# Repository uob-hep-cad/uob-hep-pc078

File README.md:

# uob-hep-pc078

XLZD OD preamplifier based on XENONnT design

Based on circuit in J. Wulf, Direct Dark Matter Search with XENON1T and Developments for Multi-Ton Liquid Xenon Detectors

[Circuit Schematic](./hardware/KiCAD/xlzd_xenonnt_amplifier_test/xlzd_xenonnt_amplifier_test_schematic_8jun26_01.pdf)

3D rendering of PCB:

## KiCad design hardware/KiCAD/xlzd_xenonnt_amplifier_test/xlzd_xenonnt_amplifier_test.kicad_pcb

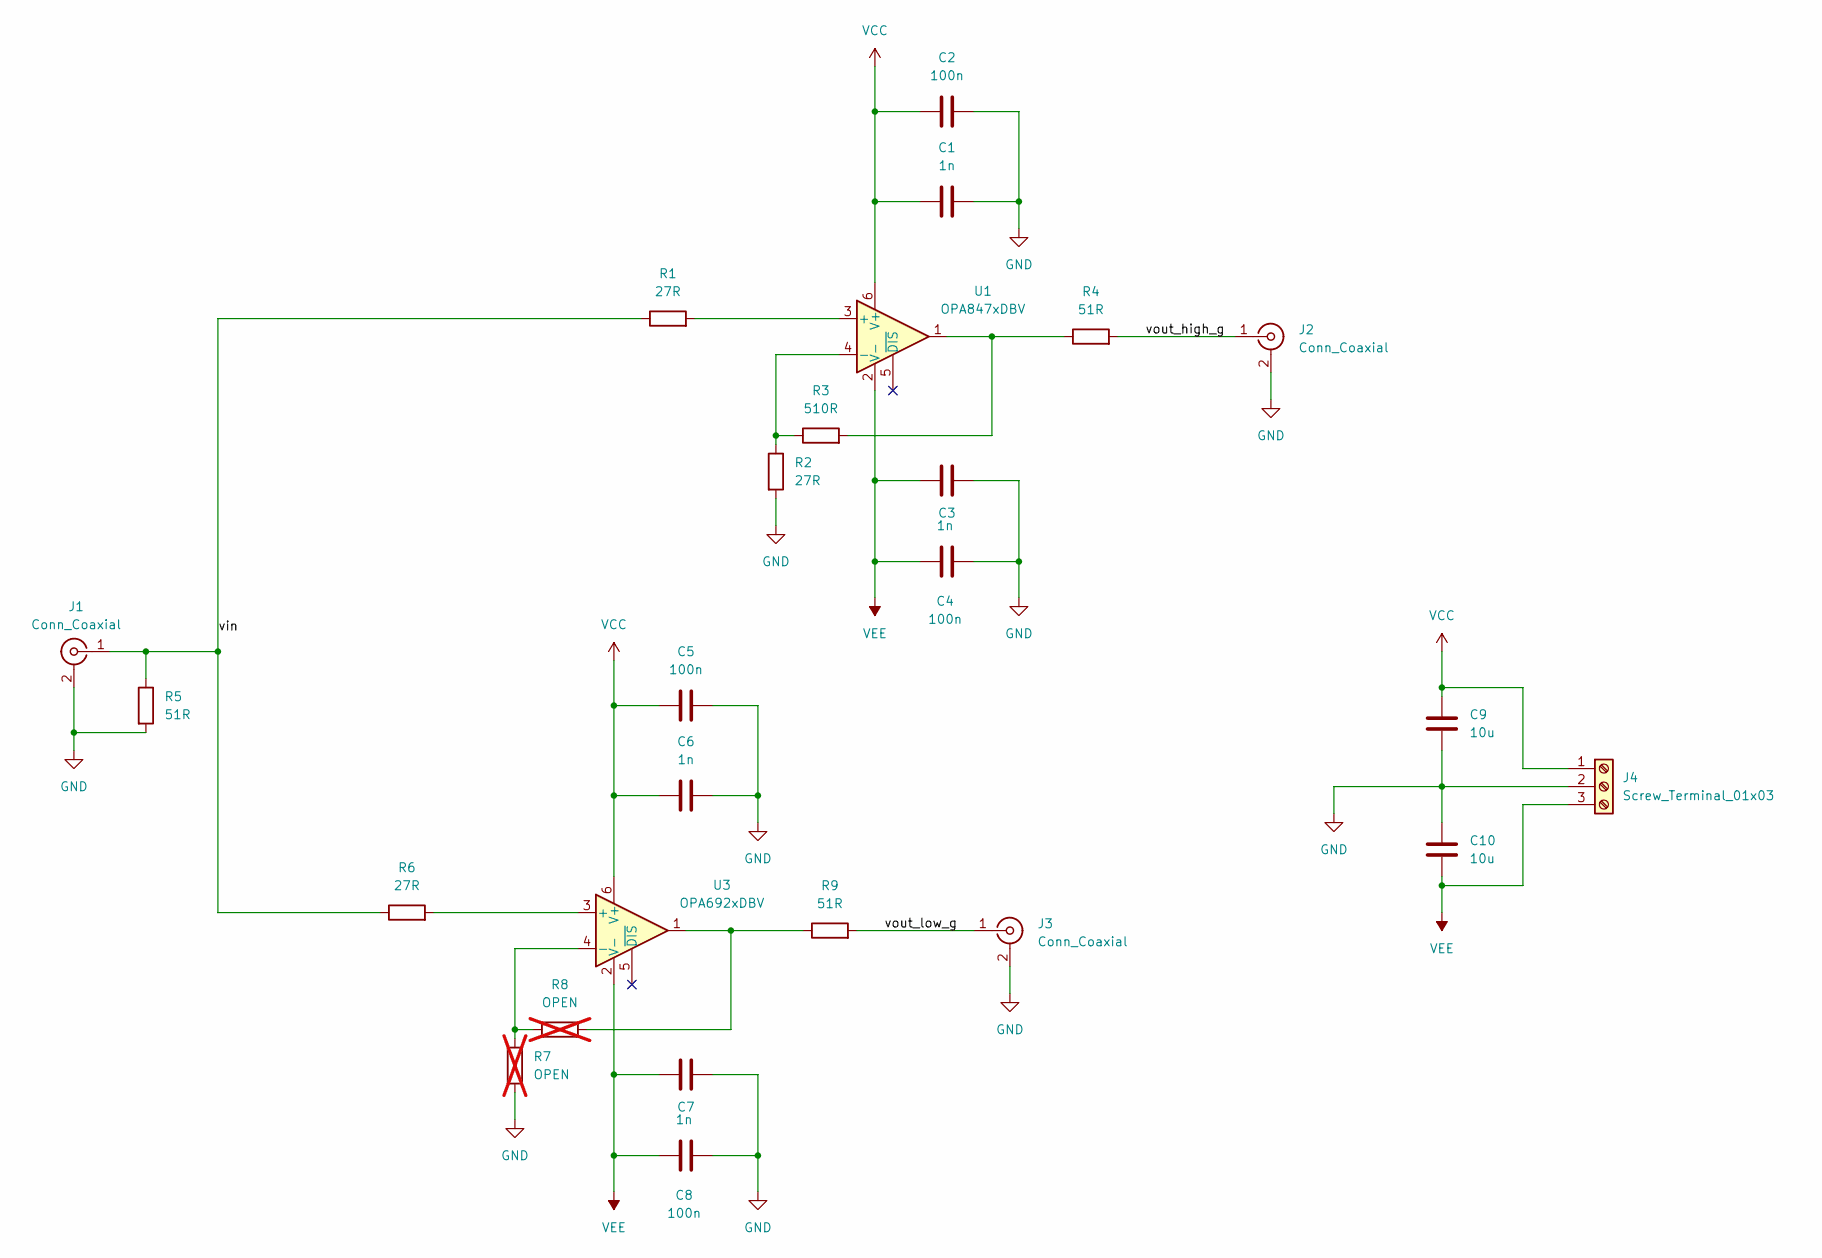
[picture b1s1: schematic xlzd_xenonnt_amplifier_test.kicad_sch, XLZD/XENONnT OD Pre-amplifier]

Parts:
C1, C3, C6, C7: 1n; C_0402_1005Metric_Pad0.74x0.62mm_HandSolder
C2, C4, C5, C8: 100n; C_0603_1608Metric_Pad1.08x0.95mm_HandSolder
C9, C10: 10u; C_1210_3225Metric_Pad1.33x2.70mm_HandSolder
J1, J2, J3: Conn_Coaxial; SMA_Amphenol_132289_EdgeMount
J4: Screw_Terminal_01x03; TerminalBlock_Phoenix_MPT-0,5-3-2.54_1x03_P2.54mm_Horizontal
R1, R2, R6: 27R; R_0603_1608Metric_Pad0.98x0.95mm_HandSolder
R3: 510R; R_0603_1608Metric_Pad0.98x0.95mm_HandSolder
R4, R5, R9: 51R; R_0603_1608Metric_Pad0.98x0.95mm_HandSolder
R7, R8: OPEN; R_0603_1608Metric_Pad0.98x0.95mm_HandSolder; not fitted
U1: OPA847xDBV; SOT-23-6
U3: OPA692xDBV; SOT-23-6

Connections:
/vin: J1.1 (In), R1.1, R5.1, R6.1
/vout_high_g: J2.1 (In), R4.2
/vout_low_g: J3.1 (In), R9.2
GND: C1.2, C2.2, C3.2, C4.2, C5.2, C6.2, C7.2, C8.2, C9.2, C10.1, J1.2 (Ext), J2.2 (Ext), J3.2 (Ext), J4.2, R2.2, R5.2, R7.2
unnamed: R3.2, R4.1, U1.1
unnamed: R8.2, R9.1, U3.1
unnamed: R1.2, U1.3 (+)
unnamed: R2.1, R3.1, U1.4 (-)
unnamed: R6.2, U3.3 (+)
unnamed: R7.1, R8.1, U3.4 (-)
VCC: C1.1, C2.1, C5.1, C6.1, C9.1, J4.1, U1.6 (V+), U3.6 (V+)
VEE: C3.1, C4.1, C7.1, C8.1, C10.2, J4.3, U1.2 (V-), U3.2 (V-)

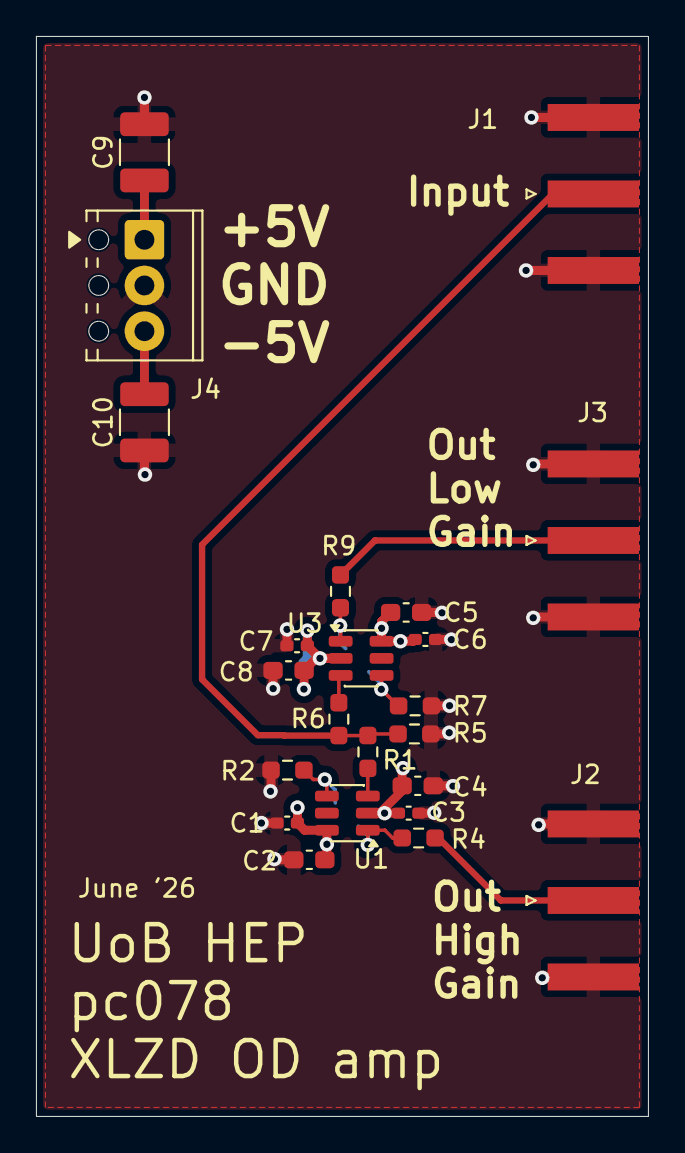
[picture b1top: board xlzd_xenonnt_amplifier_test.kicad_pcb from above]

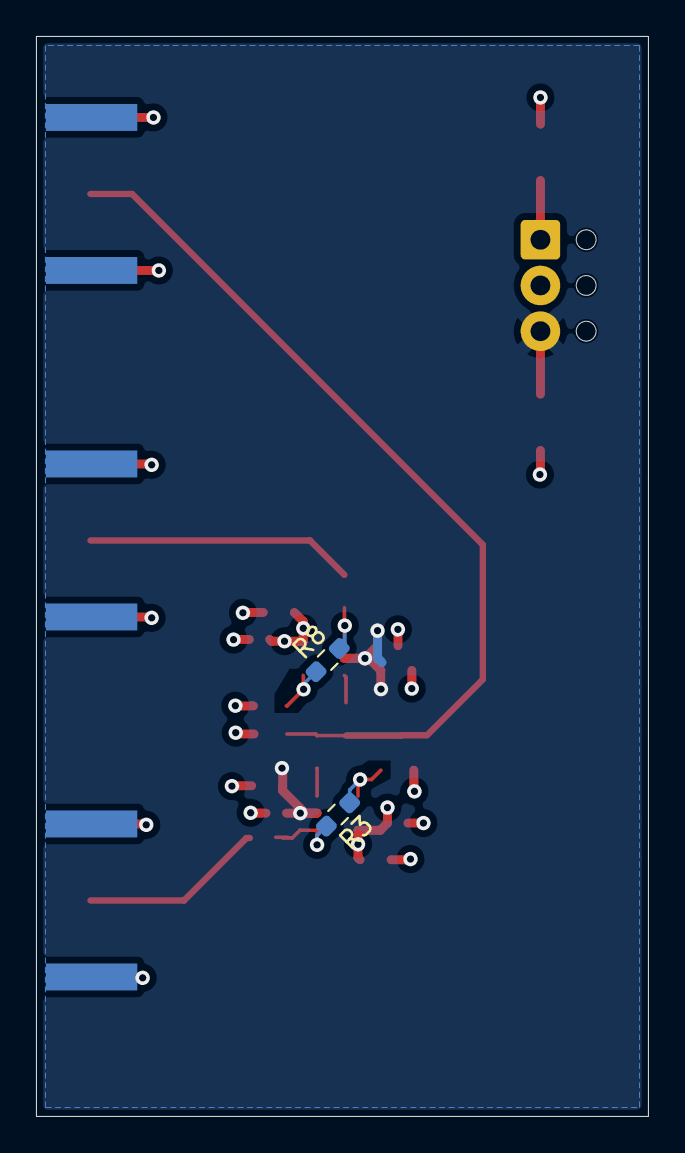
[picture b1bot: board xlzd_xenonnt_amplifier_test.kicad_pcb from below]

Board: 4 copper layers, 34.0 x 60.0 mm, 25 parts (2 on the bottom side), 12 nets.

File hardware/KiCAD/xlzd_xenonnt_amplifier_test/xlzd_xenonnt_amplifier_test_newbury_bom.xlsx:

Description | Qty per BOM | Quantity per batch | Min Quantity to order | Manufacturer | Manufacturer Part Number | Supplier | Supplier Part Number | Designator | Package Type | Technology | Comment | Status | Original Manufacturer Part No from client BOM
CAPACITOR; 0402; 50V; 10%; X7R; -55+125C | 4 | 12 | 12 |  | 0402-1nF-50V | Newbury free stock | 0402-1nF-50V | C1,C3,C6,C7 |  | SMD |  | Newbury free stock | 1n
CAPACITOR; 0603; 50V; 10%; X7R; -55+125C | 4 | 12 | 12 |  | 0603-100nF-50V | Newbury free stock | 0603-100nF-50V | C2,C4,C5,C8 |  | SMD |  | Newbury free stock | 100n
1210 10UF 50V 20% X7R | 2 | 6 | 6 | KYOCERA AVX | 12105C106MAT2A | ANGLIA | 961002001 | C9,C10 | Tape & Reel | SMD |  | Found | 10u
CONN SMA RCPT STR 50OHM EDGE MNT | 3 | 9 | 9 | Amphenol RF | 132289 | DIGIKEY | ACX1426-ND | J1,J2,J3 | Bag | SMD |  | Found | Conn_Coaxial
Conn PC Terminal Block 3 POS 2.54mm Solder ST Thru-Hole 6A | 1 | 3 | 3 | Phoenix Contact | MPT 0.5/ 3-2.54 | ARROW | 0323_01944018 | J4 | BOX | THT |  | Found | Screw_Terminal_01x03
RESISTOR; 0603; 0.1W; 100ppm; 1%; 75V; -55+125C | 3 | 9 | 9 |  | 0603-27R | Newbury free stock | 0603-27R | R1,R2,R6 |  | SMD |  | Newbury free stock | 27R
RESISTOR; 0201; 0.05W; 200ppm; 1%; 25V; -55+125C; | 1 | 3 | 3 |  | 0201-510R | Newbury free stock | 0201-510R | R3 |  | SMD |  | Newbury free stock | 510R
RESISTOR; 0603; 0.1W; 100ppm; 1%; 75V; -55+125C | 3 | 9 | 9 |  | 0603-51R | Newbury free stock | 0603-51R | R4,R5,R9 |  | SMD |  | Newbury free stock | 51R
TEXAS INSTRUMENTS - OPA847IDBVT - Operational Amplifier, 1 Channels, 3.9 GHz, 9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 | 1 | 3 | 3 | TEXAS INSTRUMENTS | OPA847IDBVT | FARNELL | 3005071 | U1 | Cut Tape | SMD |  | Found | OPA847xDBV
Video Amplifiers Wideband Fixed Gain Buffer A 595-OPA692I A 595-OPA692IDBVT | 1 | 3 | 3 | Texas Instruments | OPA692IDBVR | MOUSER | 595-OPA692IDBVR | U3 | Cut Tape | SMD |  | Found | OPA692xDBV

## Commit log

2026-06-08 First commit. PCB routed.
2026-06-08 Generated manufacturing artwork
2026-06-08 Tidied up silkscreen. Added fabrication drawings to Gerber job
2026-06-11 Added 3D render
2026-06-11 More-or-less sorted out links to schematic and 3D render (Update README.md)
2026-06-11 Increasing resolution on 3D render
2026-06-12 Added voids to planes underneath inverting input to op-amps. Regenerated artwork. Created Zip archive
